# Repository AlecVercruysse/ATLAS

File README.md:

# ATLAS: Audio Tracking Laser-Assisted Light Show

Arya Goutam and Alec Vercruysse

---

This work, completed as a final project for E155 at Harvey Mudd College, takes in music input via a 3.5mm audio jack, and syncs
a diffraction-grating based laser light show to respond to percussive elements in the song. Read our [final report](papers/report.pdf) for a description of 
the design and algorithm.

Due to the requirements of the project for the class, all SystemVerilog code, including that for the FFT, was written from scratch.

 - `fpga/` contains the SystemVerilog code used to interface with the PCM1808 ADC, the FFT module, and the beat tracking algorithm. It also includes the python files used to generate the twiddle and hann windowing look up tables.
 - `mcu/` contains the code for the microcontroller, which was responsible for selecting patterns, driving the servo, and controlling the relays.
 - `adc/` contains the design files for the PCB developed to interface the ADC with the development platform we used for the class
 - `papers/` contains the initial project proposal and final report
 - `sim/` contains the jupyter notebooks used to prototype different parts of the design.

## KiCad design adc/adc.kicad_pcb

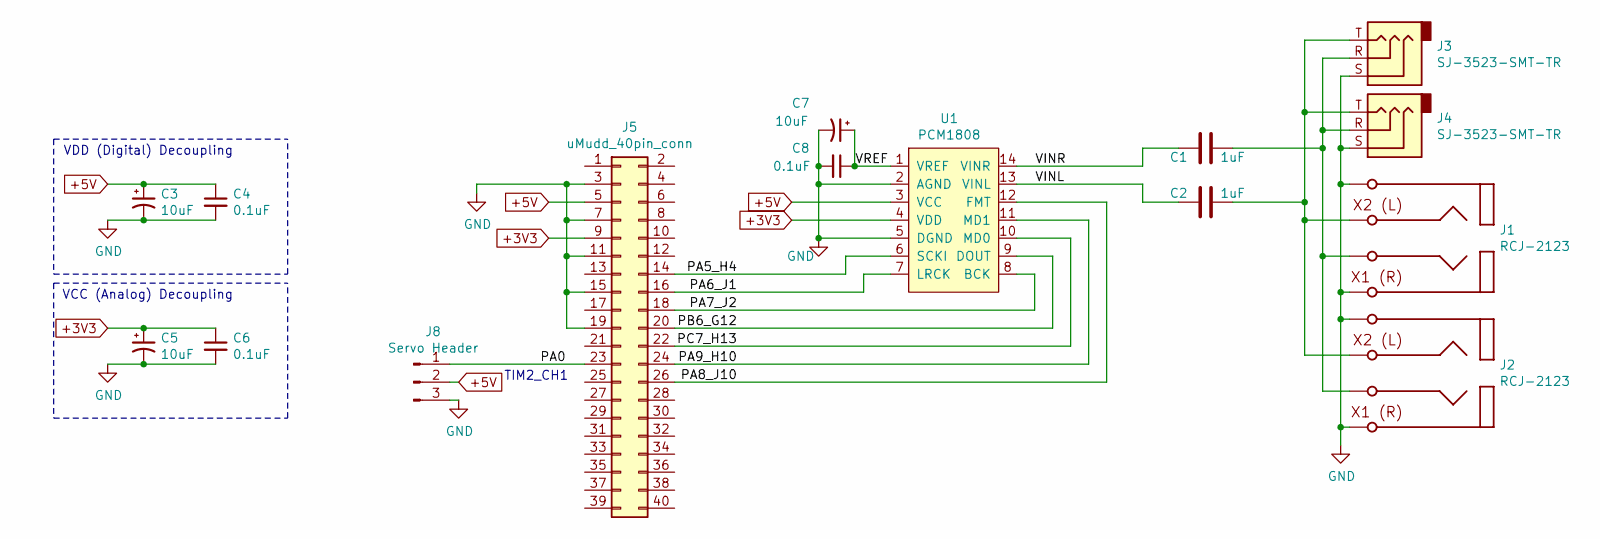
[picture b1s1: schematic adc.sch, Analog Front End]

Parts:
C1, C2: 1uF; C_0805_2012Metric_Pad1.18x1.45mm_HandSolder
C3, C5, C7: 10uF; C_0805_2012Metric_Pad1.18x1.45mm_HandSolder
C4, C6, C8: 0.1uF; C_0805_2012Metric_Pad1.18x1.45mm_HandSolder
J1, J2: RCJ-2123; Coaxial-RCJ-2123
J3, J4: SJ-3523-SMT-TR; Jack_3.5mm_CUI_SJ-3523-SMT_Horizontal
J5: uMudd_40pin_conn; S9175-ND
J8: Servo Header; PinHeader_1x03_P2.54mm_Vertical
U1: PCM1808; TSSOP-14_4.4x5mm_P0.65mm

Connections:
+3V3: C5.1, C6.1, J5.9, U1.4 (VDD)
+5V: C3.1, C4.1, J5.5, J8.2, U1.3 (VCC)
/PA0: J5.23, J8.1
/PA5_H4: J5.14, U1.6 (SCKI)
/PA6_J1: J5.16, U1.7 (LRCK)
/PA7_J2: J5.18, U1.8 (BCK)
/PA8_J10: J5.26, U1.12 (FMT)
/PA9_H10: J5.24, U1.11 (MD1)
/PB6_G12: J5.20, U1.9 (DOUT)
/PC7_H13: J5.22, U1.10 (MD0)
/VINL: C2.2, U1.13 (VINL)
/VINR: C1.2, U1.14 (VINR)
/VREF: C7.1, C8.1, U1.1 (VREF)
GND: C3.2, C4.2, C5.2, C6.2, C7.2, C8.2, J1.1, J1.3, J2.1, J2.3, J3.S, J4.S, J5.3, J5.7, J5.11, J5.15, J5.19, J8.3, U1.2 (AGND), U1.5 (DGND)
unnamed: C1.1, J1.2, J2.2, J3.R, J4.R
unnamed: C2.1, J1.4, J2.4, J3.T, J4.T

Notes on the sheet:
TIM2_CH1
VCC (Analog) Decoupling
VDD (Digital) Decoupling

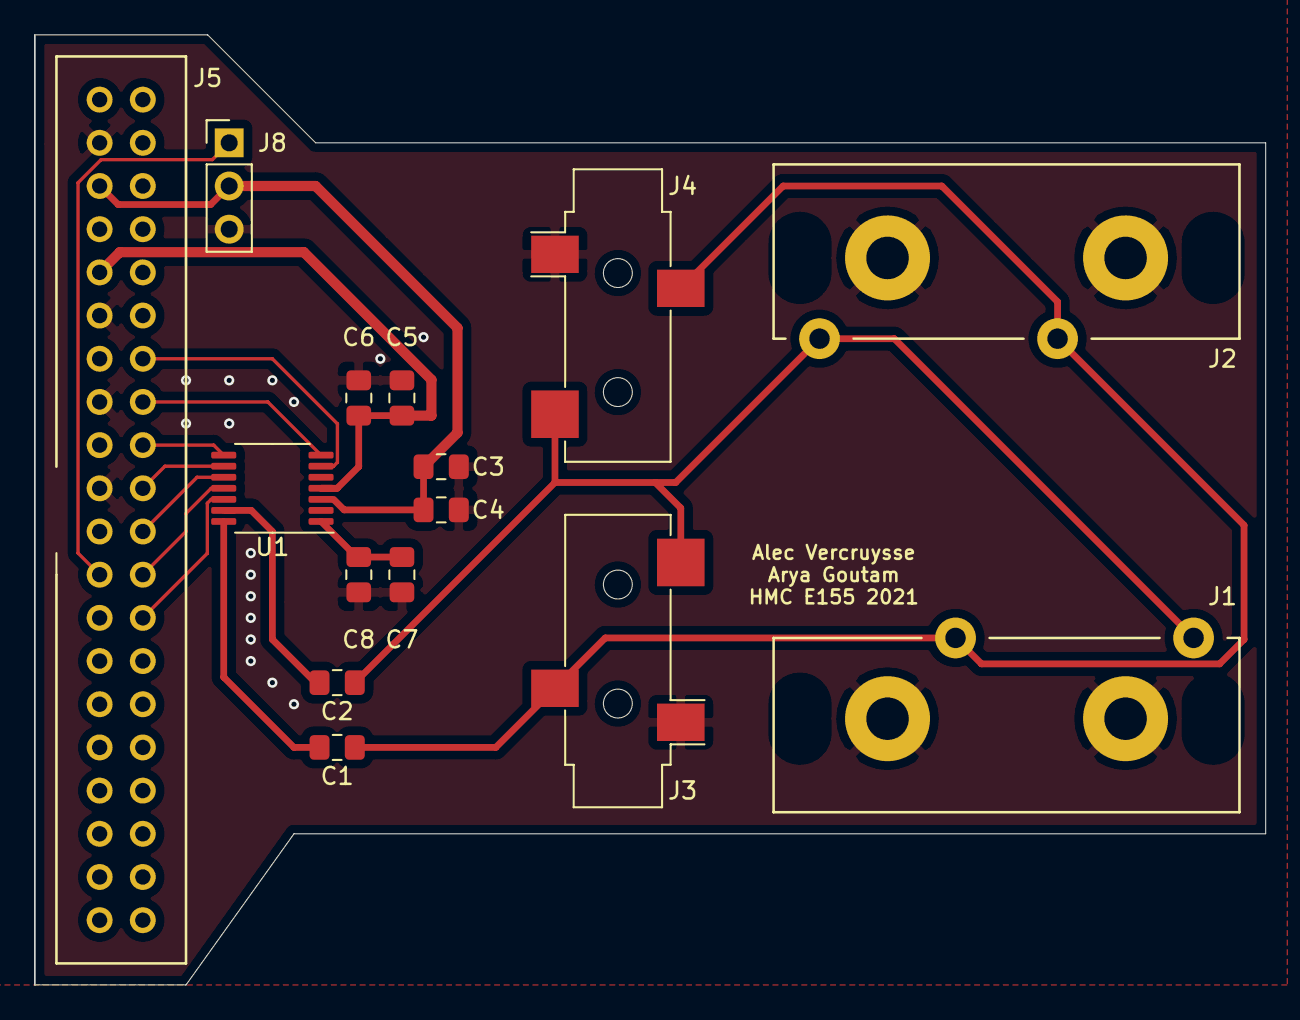
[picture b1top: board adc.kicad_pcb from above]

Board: 4 copper layers, 72.4 x 55.9 mm, 15 parts (0 on the bottom side), 16 nets.

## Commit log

2021-11-11 test in quartus
2021-11-15 make i2s more synchronous, assign pins, start fft
2021-11-15 hann window LUT
2021-11-16 twiddle vectors and change hann to signed
    - we need to be careful about the signed vs unsigned stuff.
    - I think we might want to make the hann stuff unsigned, then convert
    - unsigned to signed when we load it into the fft ram!
2021-11-18 flesh out structure and work on twiddle/hann ROM
    - bit growth might be an issue
2021-11-19 compile some fft moduled (untested)
2021-11-20 test fpga butterfly
2021-11-20 switch to 32-point FFT
2021-11-20 verify RAM
2021-11-21 pin planning
2021-11-21 untested rewrite of bgu (correct normalization)
    - also replace twiddle coeffs with slade table II
2021-11-22 verify new BGU implementation
2021-11-22 adding untested AGU code
2021-11-22 agu compiles now
2021-11-22 untested load logic
2021-11-22 get (untested) load logic to compile
2021-11-22 working
2021-11-22 agu testbench compiles now
2021-11-22 untested uncompiled fft load/out logic
2021-11-22 implement slade 32-point testbench
2021-11-22 agu sims correctly?
2021-11-22 debug fft.
2021-11-22 fix delayed twiddle buggit add fpga/fft.sv
2021-11-30 indentation! & auto gen hann/twiddle rom sim files
2021-11-30 fix incorrect imag fft sign (fix twiddle bits)
2021-11-30 i2s -> fft glue logic, verified only one cycle
2021-12-06 get working spectrum output via SPI/mcu -> uart/PC
2021-12-06 code cleanup + beat tracking algorithm prototyping
2021-12-07 adding servo code
2021-12-07 develop >10kHz-based beat tracking alg.
    - the beat tracking algorithm works ok, but it is super sensitive to
    things like the input volume unfortunately. It also really doesn't
    work well for songs without percussive elements, or even songs with
    percussive elements that are mastered to remove some of the
    highs. Moreover, this tracks highs (so that it doesn't pickup voice)
    which usually correspond to things like claps and hi-hats which
2021-12-07 fix comment in twiddle.py
    (no longer using Slade's equations, using the proper sign for the imaginary part)
2021-12-07 Working beat signal -> pattern code
2021-12-07 adding c++ implementation of fft used to verify verilog, as well as code that runs on Arduino and outputs a simulated beat at varying frequencies to test pattern creation.
2021-12-08 working Servo.c
2021-12-09 comment + format SystemVerilog code
2021-12-10 adding final working lightshow code
2021-12-10 cleaned up fft test code
2021-12-11 bugfix: pattern state not toggling on beat in.
    - remove main.c, since it is not relevant. This is present in (and
    only relevant to) the fft_display branch.
2021-12-11 update LEDs only on beat (as previously)
2022-01-04 add final report
2022-01-04 rename report
